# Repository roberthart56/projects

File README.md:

# projects
rob's projects and log. 

[Digital Fabrication](./digital_fab)

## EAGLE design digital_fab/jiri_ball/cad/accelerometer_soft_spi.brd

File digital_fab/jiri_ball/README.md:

# MicroPython-RP2040

## Getting started

Notes on Micropython for RP2040.

Using xiao board.

Using PyCharm Micropython plugin. [Instructions here.](https://themachineshop.uk/getting-started-with-the-pi-pico-and-pycharm/) This works well.

[Quick reference for R2040 on Micropython site.](https://docs.micropython.org/en/latest/rp2/quickref.html#:~:text=RP2040%20has%20five%20ADC%20channels,range%20is%200%2D3.3V.)

Nice examples for output, PWM, and ADC.

SPI in MicroPython for adxl343 [from Digikey](https://www.digikey.be/en/maker/projects/raspberry-pi-pico-rp2040-spi-example-with-micropython-and-cc/9706ea0cf3784ee98e35ff49188ee045)

Pins on the adxl343 correspont to pins on the RP2040:
SCL = SCK P2, clock
SDA = MOSI P3, master TX
SDO = MISO P4, (Slave data out) Master RX
CS = Chip Select.  P1

This works, using alternate SPI0 pins.  Note that for each of two hardware SPI, there are three pin configs.

For representation of acceleration, check [adxl343 datasheet](https://www.analog.com/media/en/technical-documentation/data-sheets/adxl343.pdf)

According to the datasheet protocol, a read is done by 
 - CS low
 - Send register address, with bit 7 high for read, bit 6 optionally high for multiple bytes.
 - Read n bytes.
 - CS high.  (deassert).

In this program, data is read sequentially from six registers, using the SPI.read(n) function.  The sequential register reading is described on p13 of the adxl343 datasheet.  It requires setting the sixth bit of the register address high:  "To read or write multiple bytes in a single transmission, the multiple-byte bit, located after the R/W bit in the first byte transfer
(MB in Figure 27 to Figure 29), must be set. After the register
addressing and the first byte of data, each subsequent set of clock
pulses (eight clock pulses) causes the ADXL343 to point to the next
register for a read or write. This shifting continues until the clock
pulses cease and CS is deasserted."

[For diagram of the sequential reading of registers to get the six bytes needed for x,y, and z:](https://www.analog.com/media/en/technical-documentation/application-notes/AN-1077.pdf)

### ADXL343 Software SPI

Software SPI implemented to allow more direct routing of traces.  
[Code is here](./code/Soft_SPI_axdl343_RGB.Jan25.py).  Eagle Project [files are in CAD directory.](./cad)

## 23K256 memory chip as an example of SPI

The 23K256 is a 32KByte memory device with a limited set of commands and registers.  Good exercise for doing SPI at a low-ish level, using the MicroPython machine functions and referring to eh chip's datasheet.

[Datasheet for 23K256:](https://ww1.microchip.com/downloads/en/DeviceDoc/22100F.pdf)

Set Polarity equal to zero for this chip.  This is the level of the idle clock.  See [SPI spec for MicroPython](https://docs.micropython.org/en/latest/library/machine.SPI.html)

[Here is a code that works](./code/SPI_23K256/SPI_23K256.py) to store and retrieve numbers from the 23K256.  All operations are written out.  Next step would be to put them in functions and create a library file for this chip. 

This is a nice example of a simple but non-trivial protocol for SPI. 

## Feb 2024.

Use esp32c3 for its ability to battery manage.  Change pins and spi to use hardware spi, because that's the board that was available. This works, but gives overflow at high acc values for the PWM duty cycle.  Need to work on this, but looks like it should be solvable.  Take to Haystack.  Hope to iterate with cheaper and more reproducible solution.

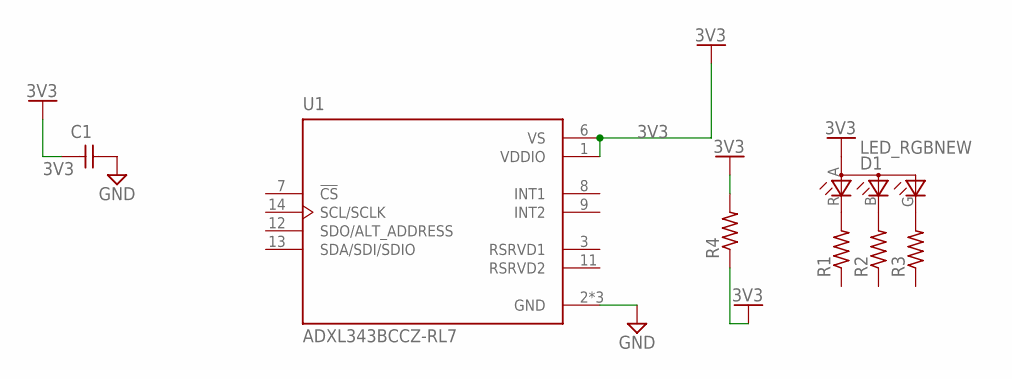
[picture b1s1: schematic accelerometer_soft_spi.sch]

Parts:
C1: CAP_UNPOLARIZED; C1206
D1: LED_RGBNEW; P-LCC-4
R1, R2, R3, R4: R1206
U1: ADXL343BCCZ-RL7; PQFN80P300X500X100-14N

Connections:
3V3: C1.1, D1.A (A2), R4.1, R4.2, U1.1 (VDDIO), U1.6 (VS)
GND: C1.2, U1.2 (GND), U1.4 (GND), U1.5 (GND)
unnamed: D1.R (CRED), R1.2
unnamed: D1.B (CBLUE), R2.2
unnamed: D1.G (CGREEN), R3.2

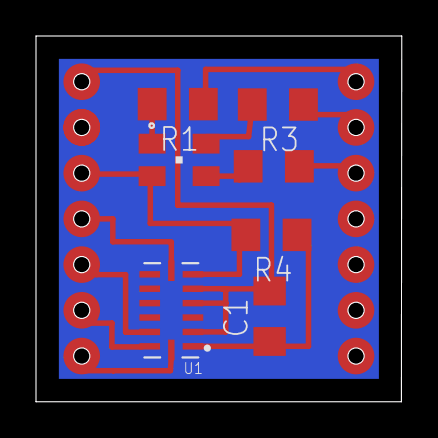
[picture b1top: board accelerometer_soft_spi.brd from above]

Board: 2 copper layers, 20.3 x 20.3 mm, 7 parts (0 on the bottom side), 5 nets.

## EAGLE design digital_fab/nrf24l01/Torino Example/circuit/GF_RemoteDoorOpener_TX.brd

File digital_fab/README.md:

# Digital Fabrication

[Haystack 2024](./haystack_2024)
[Parametric Box](./parametric_box)
[Modular Things](./modular_things)

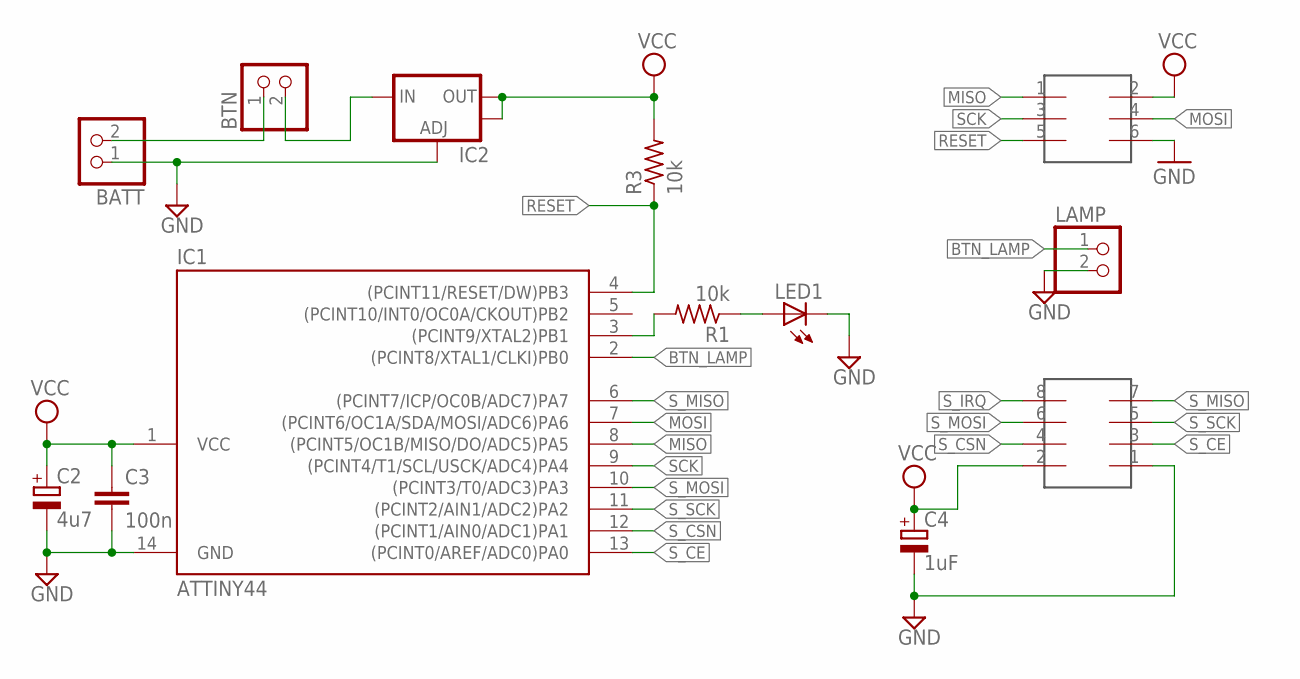
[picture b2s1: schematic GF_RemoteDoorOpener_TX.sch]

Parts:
BATT: PINHD-1X2; 1X02
BTN: PINHD-1X2; 1X02
C2: 4u7; SMC_A
C3: 100n; C0603
C4: 1uF; SMC_A
IC1: ATTINY44; SOIC14
IC2: V_REG_LM1117SOT223; SOT223
ISP: 2X3HEADER; 2X3_SMD
LAMP: PINHD-1X2; 1X02
LED1: LEDCHIPLED_1206; CHIPLED_1206
R1, R3: 10k; R0603
U$2: 2X4HEADER; 2X4_SMD

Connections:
BTN_LAMP: IC1.2 ((PCINT8/XTAL1/CLKI)PB0), LAMP.1
GND: BATT.1, C2.-, C3.2, C4.-, IC1.14 (GND), IC2.1 (ADJ), ISP.6, LAMP.2, LED1.C, U$2.1
MISO: IC1.8 ((PCINT5/OC1B/MISO/DO/ADC5)PA5), ISP.1
MOSI: IC1.7 ((PCINT6/OC1A/SDA/MOSI/ADC6)PA6), ISP.4
unnamed: BATT.2, BTN.1
unnamed: IC1.3 ((PCINT9/XTAL2)PB1), R1.2
unnamed: LED1.A, R1.1
unnamed: BTN.2, IC2.3 (IN)
RESET: IC1.4 ((PCINT11/RESET/DW)PB3), ISP.5, R3.1
SCK: IC1.9 ((PCINT4/T1/SCL/USCK/ADC4)PA4), ISP.3
S_CE: IC1.13 ((PCINT0/AREF/ADC0)PA0), U$2.3
S_CSN: IC1.12 ((PCINT1/AIN0/ADC1)PA1), U$2.4
S_IRQ: U$2.8
S_MISO: IC1.6 ((PCINT7/ICP/OC0B/ADC7)PA7), U$2.7
S_MOSI: IC1.10 ((PCINT3/T0/ADC3)PA3), U$2.6
S_SCK: IC1.11 ((PCINT2/AIN1/ADC2)PA2), U$2.5
VCC: C2.+, C3.1, C4.+, IC1.1 (VCC), IC2.2 (OUT), IC2.4 (OUT), ISP.2, R3.2, U$2.2

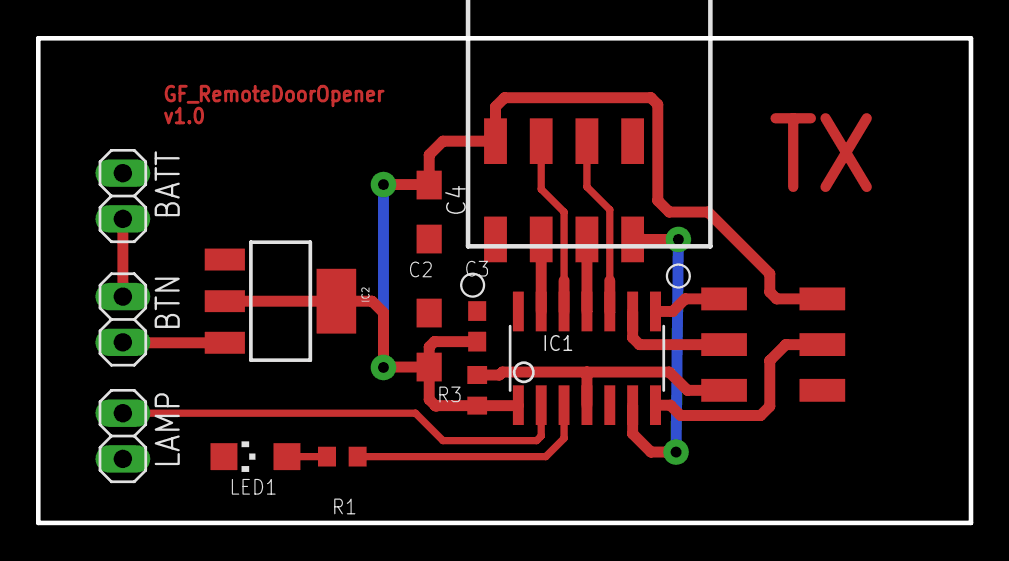
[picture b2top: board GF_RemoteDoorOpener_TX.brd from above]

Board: 2 copper layers, 51.8 x 26.9 mm, 13 parts (0 on the bottom side), 16 nets.

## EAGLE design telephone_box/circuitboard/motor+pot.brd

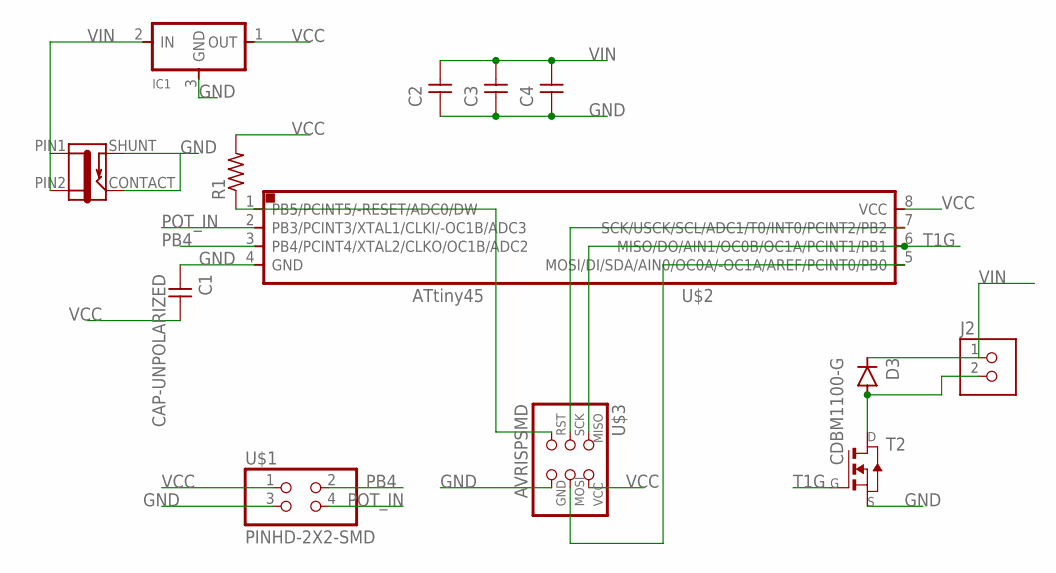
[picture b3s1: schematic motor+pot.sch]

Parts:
C1, C2, C3, C4: CAP-UNPOLARIZED; C1206
D3: CDBM1100-G; MINI-SMA
IC1: REGULATORSOT23; SOT23
J2: TERM-1X02-FABLAB; ED555DS-2DS
J3: JACK-2.1MM; PJ-002AH-SMT
R1: RES-US1206; R1206
T2: NMOSFETTO252; TO252
U$1: PINHD-2X2-SMD; 2X02SMD
U$2: ATTINY45SI; SOIC8
U$3: AVRISPSMD; 2X03SMD

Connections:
GND: C1.1, C2.1, C3.1, C4.1, IC1.3 (GND), J3.CONTACT, J3.SHUNT, T2.2 (S), U$1.3, U$2.4 (GND), U$3.6 (GND)
unnamed: U$2.5 (MOSI/DI/SDA/AIN0/OC0A/-OC1A/AREF/PCINT0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), U$3.4 (MOSI)
unnamed: R1.1, U$2.1 (PB5/PCINT5/-RESET/ADC0/DW), U$3.5 (RST)
unnamed: D3.ANODE, J2.2, T2.3 (D)
PB4: U$1.2, U$2.3 (PB4/PCINT4/XTAL2/CLKO/OC1B/ADC2)
POT_IN: U$1.4, U$2.2 (PB3/PCINT3/XTAL1/CLKI/-OC1B/ADC3)
T1G: T2.1 (G), U$2.6 (MISO/DO/AIN1/OC0B/OC1A/PCINT1/PB1), U$3.1 (MISO)
T2G: U$2.7 (SCK/USCK/SCL/ADC1/T0/INT0/PCINT2/PB2), U$3.3 (SCK)
VCC: C1.2, IC1.1 (OUT), R1.2, U$1.1, U$2.8 (VCC), U$3.2 (VCC)
VIN: C2.2, C3.2, C4.2, D3.KATHODE, IC1.2 (IN), J2.1, J3.PIN1, J3.PIN2

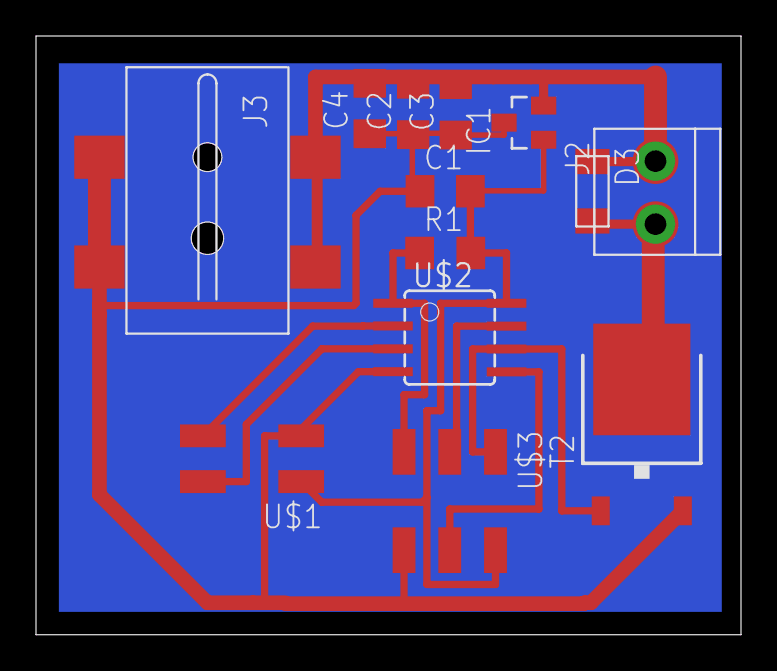
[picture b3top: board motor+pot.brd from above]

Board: 2 copper layers, 39.2 x 33.3 mm, 13 parts (0 on the bottom side), 10 nets.

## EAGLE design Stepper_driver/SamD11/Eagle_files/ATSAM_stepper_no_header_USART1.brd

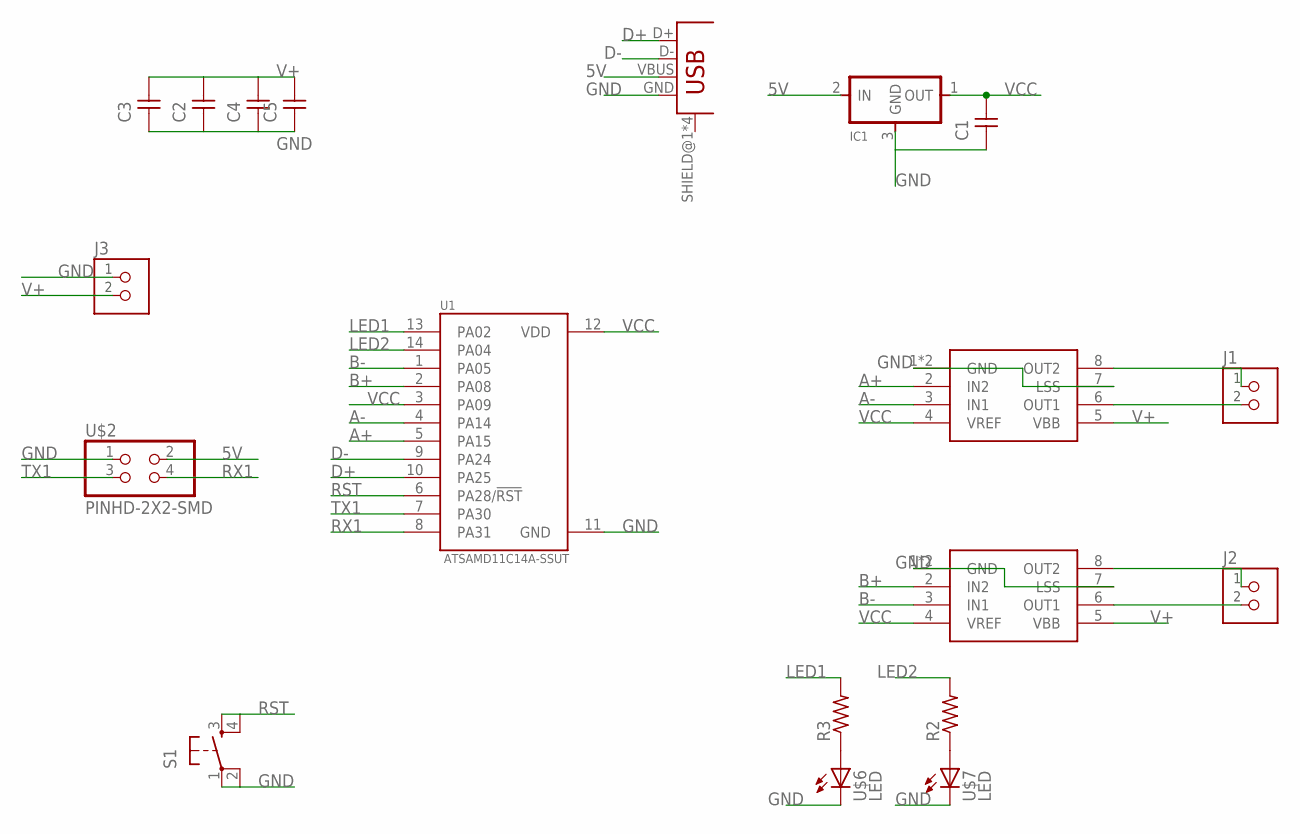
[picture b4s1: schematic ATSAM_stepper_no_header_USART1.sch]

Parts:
C1, C2, C3, C4, C5: CAP-UNPOLARIZED; C1206
IC1: VR_REGULATOR-SOT23SOT23; SOT23
J1, J2, J3: TERM-1X02-FABLAB; ED555DS-2DS
R2, R3: RES-US1206; R1206
S1: SW_SWITCH_TACTILE_6MM6MM_SWITCH; 6MM_SWITCH
U1: ATSAMD11C14A-SSUT; SOIC127P600X160-14N
U$1: CONN_USB_MINIB; USB_MINIB
U$2: PINHD-2X2-SMD; 2X02SMD
U$3, U$4: A4953-H-BRIDGE-MOTOR-DRIVER-PAD; SOIC8_PAD
U$6, U$7: LED; LED1206

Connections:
5V: IC1.2 (IN), U$1.VBUS, U$2.2
A+: U1.5 (PA15), U$3.2 (IN2)
A-: U1.4 (PA14), U$3.3 (IN1)
B+: U1.2 (PA08), U$4.2 (IN2)
B-: U1.1 (PA05), U$4.3 (IN1)
D+: U1.10 (PA25), U$1.D+
D-: U1.9 (PA24), U$1.D-
GND: C1.1, C2.1, C3.1, C4.1, C5.1, IC1.3 (GND), J3.1, S1.1, S1.2 (P1), U1.11 (GND), U$1.GND, U$2.1, U$3.1 (GND), U$3.7 (LSS), U$3.GND, U$4.1 (GND), U$4.7 (LSS), U$4.GND, U$6.2 (C), U$7.2 (C)
LED1: R3.2, U1.13 (PA02)
LED2: R2.2, U1.14 (PA04)
unnamed: R2.1, U$7.1 (A)
unnamed: J1.1, U$3.8 (OUT2)
unnamed: J1.2, U$3.6 (OUT1)
unnamed: J2.1, U$4.8 (OUT2)
unnamed: J2.2, U$4.6 (OUT1)
unnamed: R3.1, U$6.1 (A)
RST: S1.3 (S), S1.4 (S1), U1.6 (PA28/!RST)
RX1: U1.8 (PA31), U$2.4
TX1: U1.7 (PA30), U$2.3
V+: C2.2, C3.2, C4.2, C5.2, J3.2, U$3.5 (VBB), U$4.5 (VBB)
VCC: C1.2, IC1.1 (OUT), U1.3 (PA09), U1.12 (VDD), U$3.4 (VREF), U$4.4 (VREF)

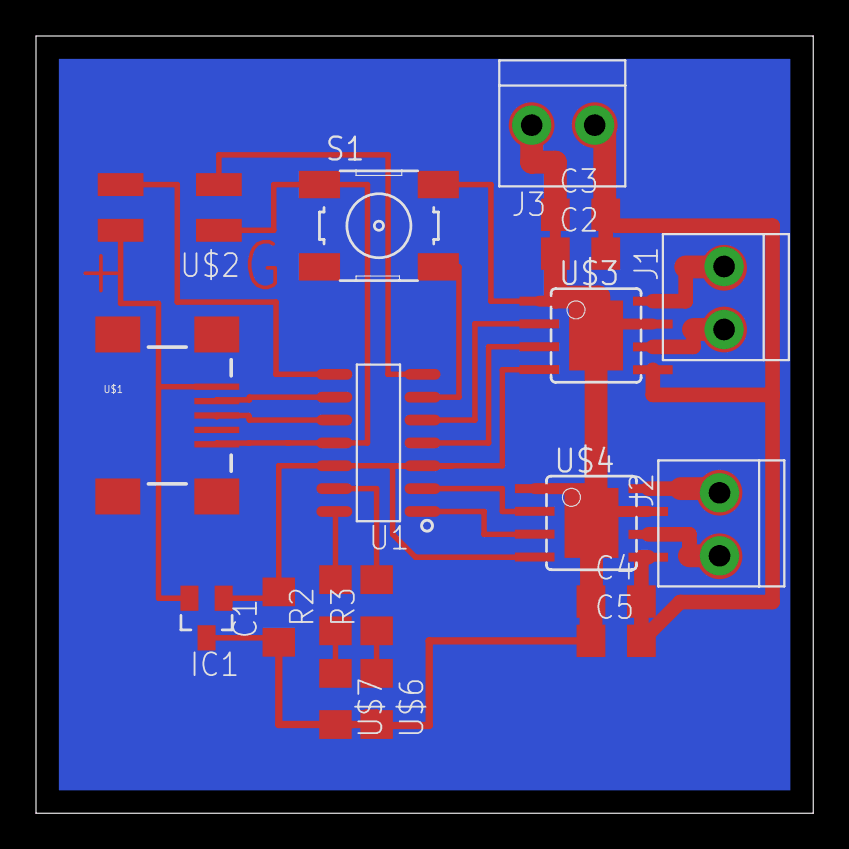
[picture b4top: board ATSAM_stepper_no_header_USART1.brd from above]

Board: 2 copper layers, 43.2 x 43.2 mm, 19 parts (0 on the bottom side), 21 nets.

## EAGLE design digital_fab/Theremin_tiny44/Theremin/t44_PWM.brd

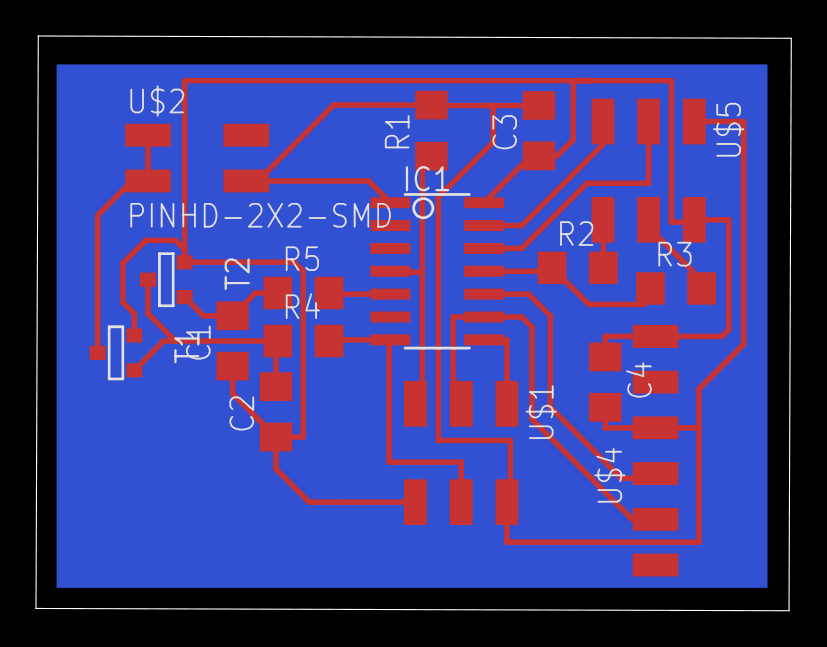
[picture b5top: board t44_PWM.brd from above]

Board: 2 copper layers, 42.0 x 31.9 mm, 16 parts (0 on the bottom side), 16 nets.

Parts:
C1, C2, C3, C4: C1206
IC1: ATTINY44-SSU; SOIC14
R1, R2, R3, R4, R5: R1206
T1, T2: SOT-23
U$1, U$5: AVRISPSMD; 2X03SMD
U$2: PINHD-2X2-SMD; 2X02SMD
U$4: FTDI-SMD-HEADER; 1X06SMD

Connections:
GND: C1.1, C2.1, C3.1, C4.1, IC1.14, T1.2, T2.2, U$1.6, U$4.1, U$5.2
unnamed: C2.2, R4.1, T1.3, T2.1
unnamed: R2.2, U$5.6
unnamed: IC1.8, U$1.1
unnamed: IC1.4, R1.1, U$1.5
unnamed: C1.2, R5.1, T2.3
unnamed: R3.2, U$5.4
unnamed: T1.1, U$2.1, U$2.3
unnamed: IC1.13, U$5.5
unnamed: IC1.12, U$5.3
unnamed: IC1.11, R2.1, R3.1
PWMFAST: IC1.5, R5.2
PWMSLOW: IC1.7, R4.2, U$1.4
RX: IC1.10, U$4.4
TX: IC1.9, U$1.3, U$4.5
VCC: C3.2, C4.2, IC1.1, R1.2, U$1.2, U$2.4, U$4.3, U$5.1

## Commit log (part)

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2019-10-24 add nrf stuff
2019-12-02 add flash project and others
2019-12-30 various additions
2020-01-08 edited and remove stepper project
2020-02-02 moved stepper out and edited telophone
2020-02-02 edited telephone box
2020-02-02 update files for telephone
2020-02-04 added fiber and edited telephone
2020-02-11 edits to telephone
2020-02-13 edtis to index and figs.
2020-04-22 add samd folder
2020-06-30 moved telephone box
2020-08-26 add clank stuff
2020-11-17 edits
2020-11-17 add Nov 2020
2020-11-18 add programming folder
2020-11-21 Create README.md
    add cooking folder
2020-11-27 Rename README.md to readme.md
2020-12-08 add ubuntu project
2020-12-08 add december log file
2020-12-15 add vial lights
2021-01-02 added freecad
2021-01-02 added freecad readme
2021-01-06 test change
2021-01-06 change 2
2021-01-06 add vial pics
2021-01-06 add pics
2021-01-06 resize
2021-01-06 add jan
2021-01-08 added machines
2021-01-13 modify
2021-01-14 add freecad parametric
2021-01-14 remove
2021-01-15 Jan15
2021-01-15 add ender3
2021-01-18 add food proc repair
2021-01-18 try again
2021-01-19 python stuff
2021-01-19 knitting
2021-01-21 edit readme001
2021-01-21 edit readme
2021-01-22 add pic
2021-01-22 resizes
2021-01-22 edit
2021-01-25 added pics dir
2021-01-25 add figlist
2021-01-25 save
2021-01-25 rotate
2021-01-29 machine
2021-02-05 added pics
2021-02-11 add directory for cbd workflow
2021-02-18 add Feb
2021-02-26 add clavichord
2021-03-01 clav
2021-04-18 add reading
2021-04-18 caps
2021-06-03 airpump edit
2021-06-11 add smaller
2021-06-15 start organ page
2021-07-13 lkkj
2021-07-14 added code
2021-07-17 Create notes_7_16
2021-07-24 Create notes_7_24
2021-07-24 Update notes_7_24
2021-07-24 Rename notes_7_24 to notes_7_24.md
2021-07-24 Update notes_7_24.md
    attempt to add photo to markdown file
2021-07-28 added hall switch
2021-07-28 add picture and README
2021-07-28 edit1
2021-08-17 software
2021-08-17 new notes
2021-08-18 Create new_pictures_8_18.md
    new pictures
2021-08-18 Update new_pictures_8_18.md
    recent pictures added. Pedalboard with all sensors in place. half of the pedals are 'ribboned'. testing/calibrating imminent!
2021-08-19 add MIDI_Mega
2021-09-13 add programming links
2021-09-15 add kicad notes
2021-09-26 added garden
2022-01-20 update from windows
2022-01-20 add 2022 log
2022-01-20 edit log
2022-03-02 added error text
2022-03-02 add to text
2022-03-21 added sketch
2022-03-21 added pic
2022-07-07 add stuff
2022-11-10 add DICE folder
2023-02-02 add soil life
2023-03-28 add resonator
2023-03-28 edits and additions
2023-09-04 add haystack2023
2023-11-06 rearrange folders
2023-11-07 add material
2024-03-14 adding new folders
2024-08-27 various edits
2024-08-27 add maxl
2024-09-29 update changes
2024-11-12 added organ 2024
2024-12-05 add organ 2024 stuff
2025-01-20 edits and moving and Repair folder
2025-03-21 trying after reinstall
2026-02-17 added color clock
2026-02-17 added code and pic
2026-06-11 added clock pic

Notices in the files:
parts and their libraries:
SparkFun-PowerIC: Licensing: CC v3.0 Share-Alike You are welcome to use this library for commercial purposes.
